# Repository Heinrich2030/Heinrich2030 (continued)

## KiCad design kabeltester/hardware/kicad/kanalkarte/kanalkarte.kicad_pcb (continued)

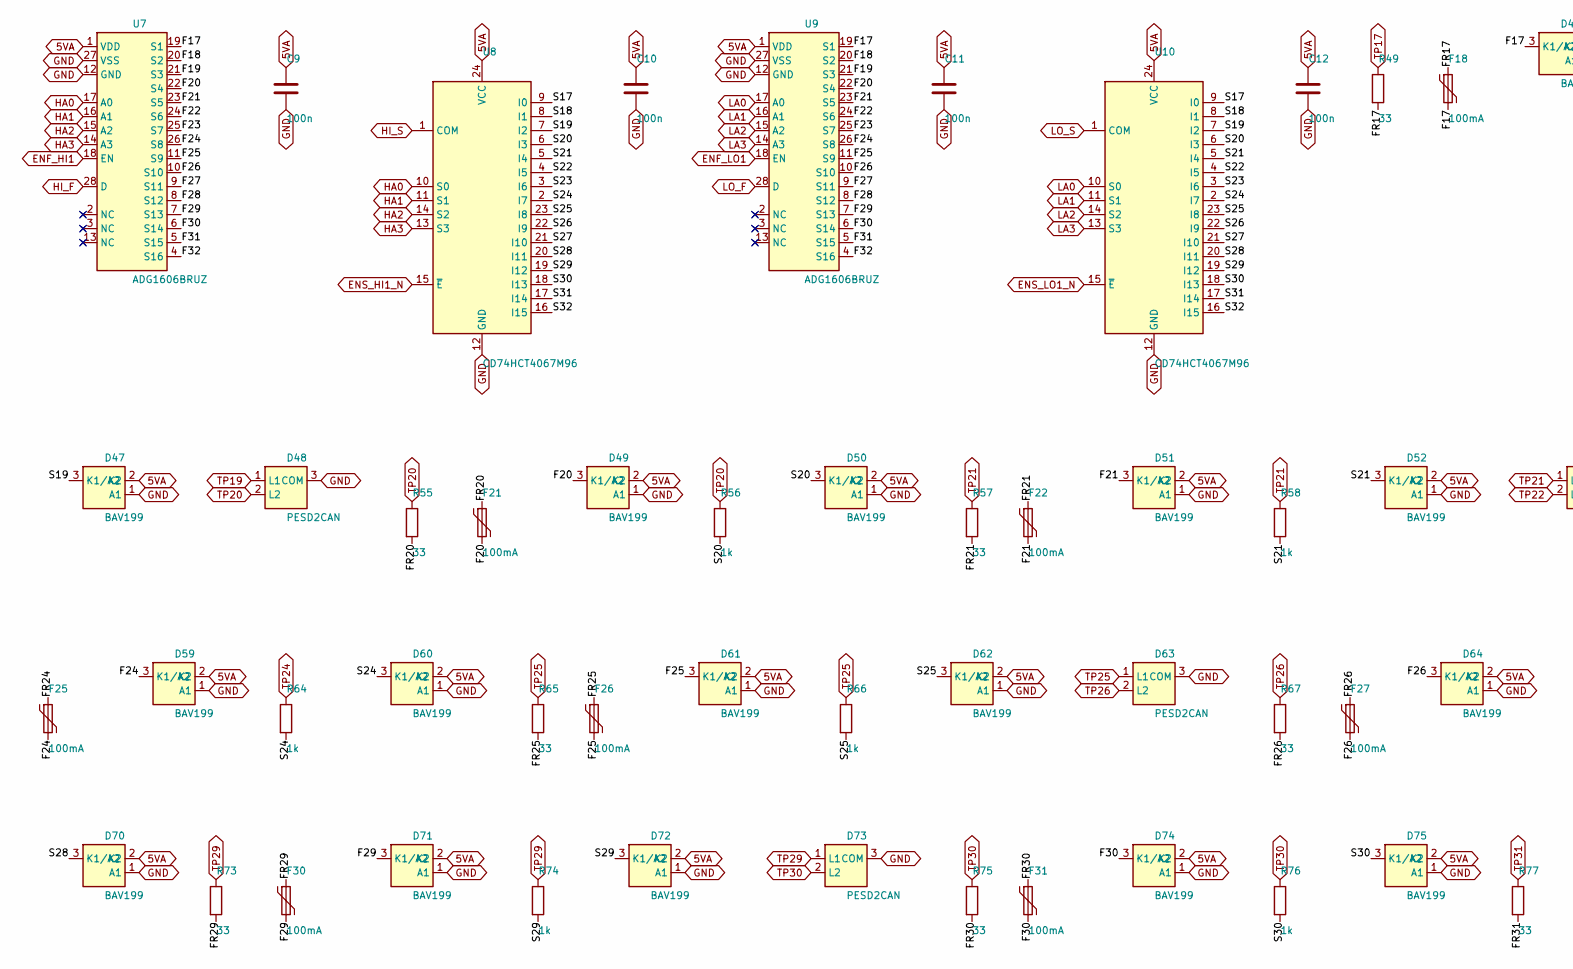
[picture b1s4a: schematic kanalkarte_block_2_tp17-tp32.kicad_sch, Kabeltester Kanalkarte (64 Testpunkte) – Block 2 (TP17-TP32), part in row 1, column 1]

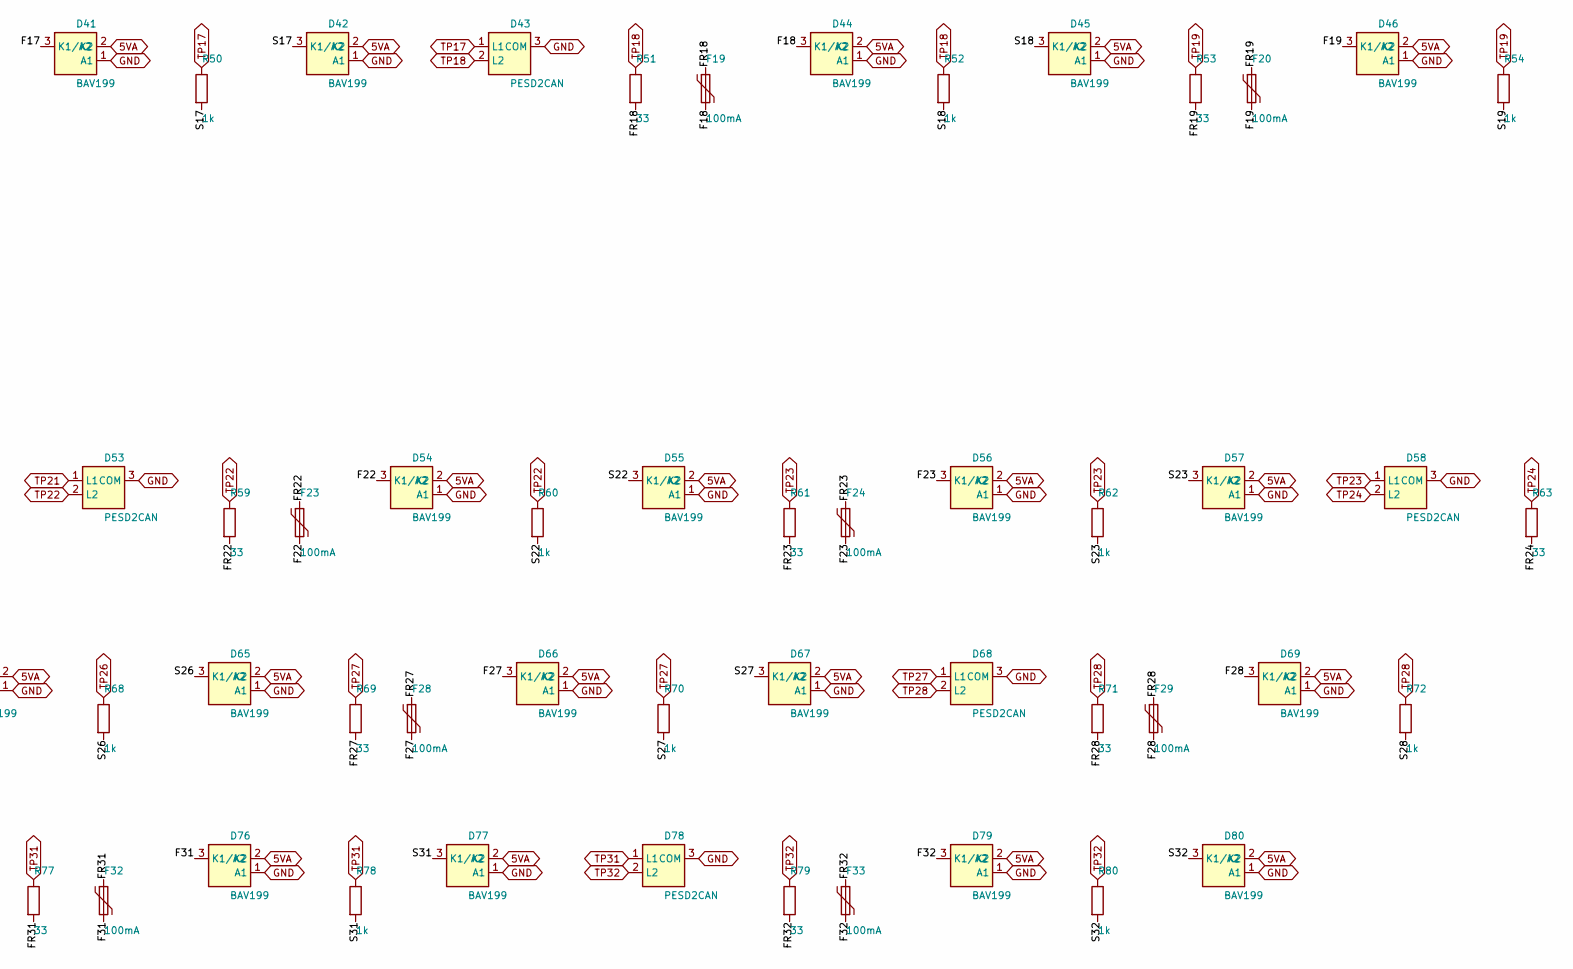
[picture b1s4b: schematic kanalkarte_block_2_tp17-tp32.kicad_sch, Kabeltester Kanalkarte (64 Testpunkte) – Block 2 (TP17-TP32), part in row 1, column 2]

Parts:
C9, C10, C11, C12: 100n; C_0603_1608Metric; LCSC C14663
D41, D42, D44, D45, D46, D47, D49, D50, D51, D52, D54, D55, D56, D57, D59, D60, D61, D62, D64, D65, D66, D67, D69, D70, D71, D72, D74, D75, D76, D77, D79, D80: BAV199; SOT-23
D43, D48, D53, D58, D63, D68, D73, D78: PESD2CAN; SOT-23
F18, F19, F20, F21, F22, F23, F24, F25, F26, F27, F28, F29, F30, F31, F32, F33: 100mA; Fuse_1206_3216Metric; MPN Bourns MF-USMF010-2
R49, R51, R53, R55, R57, R59, R61, R63, R65, R67, R69, R71, R73, R75, R77, R79: 33; R_1206_3216Metric; MPN CRCW120633R0FKEAHP
R50, R52, R54, R56, R58, R60, R62, R64, R66, R68, R70, R72, R74, R76, R78, R80: 1k; R_0603_1608Metric; LCSC C21190
U7, U9: ADG1606BRUZ; TSSOP-28_4.4x9.7mm_P0.65mm; LCSC C208204
U8, U10: CD74HCT4067M96; SOIC-24W_7.5x15.4mm_P1.27mm

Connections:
5VA: C9.1, C10.1, C11.1, C12.1, D41.2 (K2), D42.2 (K2), D44.2 (K2), D45.2 (K2), D46.2 (K2), D47.2 (K2), D49.2 (K2), D50.2 (K2), D51.2 (K2), D52.2 (K2), D54.2 (K2), D55.2 (K2), D56.2 (K2), D57.2 (K2), D59.2 (K2), D60.2 (K2), D61.2 (K2), D62.2 (K2), D64.2 (K2), D65.2 (K2), D66.2 (K2), D67.2 (K2), D69.2 (K2), D70.2 (K2), D71.2 (K2), D72.2 (K2), D74.2 (K2), D75.2 (K2), D76.2 (K2), D77.2 (K2), D79.2 (K2), D80.2 (K2), U7.1 (VDD), U8.24 (VCC), U9.1 (VDD), U10.24 (VCC); also elsewhere on the board
ENF_HI1: U7.18 (EN); also elsewhere on the board
ENF_LO1: U9.18 (EN); also elsewhere on the board
ENS_HI1_N: U8.15 (~E); also elsewhere on the board
ENS_LO1_N: U10.15 (~E); also elsewhere on the board
F17: D41.3 (K1/A2), F18.2, U7.19 (S1), U9.19 (S1)
F18: D44.3 (K1/A2), F19.2, U7.20 (S2), U9.20 (S2)
F19: D46.3 (K1/A2), F20.2, U7.21 (S3), U9.21 (S3)
F20: D49.3 (K1/A2), F21.2, U7.22 (S4), U9.22 (S4)
F21: D51.3 (K1/A2), F22.2, U7.23 (S5), U9.23 (S5)
F22: D54.3 (K1/A2), F23.2, U7.24 (S6), U9.24 (S6)
F23: D56.3 (K1/A2), F24.2, U7.25 (S7), U9.25 (S7)
F24: D59.3 (K1/A2), F25.2, U7.26 (S8), U9.26 (S8)
F25: D61.3 (K1/A2), F26.2, U7.11 (S9), U9.11 (S9)
F26: D64.3 (K1/A2), F27.2, U7.10 (S10), U9.10 (S10)
F27: D66.3 (K1/A2), F28.2, U7.9 (S11), U9.9 (S11)
F28: D69.3 (K1/A2), F29.2, U7.8 (S12), U9.8 (S12)
F29: D71.3 (K1/A2), F30.2, U7.7 (S13), U9.7 (S13)
F30: D74.3 (K1/A2), F31.2, U7.6 (S14), U9.6 (S14)
F31: D76.3 (K1/A2), F32.2, U7.5 (S15), U9.5 (S15)
F32: D79.3 (K1/A2), F33.2, U7.4 (S16), U9.4 (S16)
FR17: F18.1, R49.2
FR18: F19.1, R51.2
FR19: F20.1, R53.2
FR20: F21.1, R55.2
FR21: F22.1, R57.2
FR22: F23.1, R59.2
FR23: F24.1, R61.2
FR24: F25.1, R63.2
FR25: F26.1, R65.2
FR26: F27.1, R67.2
FR27: F28.1, R69.2
FR28: F29.1, R71.2
FR29: F30.1, R73.2
FR30: F31.1, R75.2
FR31: F32.1, R77.2
FR32: F33.1, R79.2
GND: C9.2, C10.2, C11.2, C12.2, D41.1 (A1), D42.1 (A1), D43.3 (COM), D44.1 (A1), D45.1 (A1), D46.1 (A1), D47.1 (A1), D48.3 (COM), D49.1 (A1), D50.1 (A1), D51.1 (A1), D52.1 (A1), D53.3 (COM), D54.1 (A1), D55.1 (A1), D56.1 (A1), D57.1 (A1), D58.3 (COM), D59.1 (A1), D60.1 (A1), D61.1 (A1), D62.1 (A1), D63.3 (COM), D64.1 (A1), D65.1 (A1), D66.1 (A1), D67.1 (A1), D68.3 (COM), D69.1 (A1), D70.1 (A1), D71.1 (A1), D72.1 (A1), D73.3 (COM), D74.1 (A1), D75.1 (A1), D76.1 (A1), D77.1 (A1), D78.3 (COM), D79.1 (A1), D80.1 (A1), U7.12 (GND), U7.27 (VSS), U8.12 (GND), U9.12 (GND), U9.27 (VSS), U10.12 (GND); also elsewhere on the board
HA0: U7.17 (A0), U8.10 (S0); also elsewhere on the board
HA1: U7.16 (A1), U8.11 (S1); also elsewhere on the board
HA2: U7.15 (A2), U8.14 (S2); also elsewhere on the board
HA3: U7.14 (A3), U8.13 (S3); also elsewhere on the board
HI_F: U7.28 (D); also elsewhere on the board
HI_S: U8.1 (COM); also elsewhere on the board
LA0: U9.17 (A0), U10.10 (S0); also elsewhere on the board
LA1: U9.16 (A1), U10.11 (S1); also elsewhere on the board
LA2: U9.15 (A2), U10.14 (S2); also elsewhere on the board
LA3: U9.14 (A3), U10.13 (S3); also elsewhere on the board
LO_F: U9.28 (D); also elsewhere on the board
LO_S: U10.1 (COM); also elsewhere on the board
S17: D42.3 (K1/A2), R50.2, U8.9 (I0), U10.9 (I0)
S18: D45.3 (K1/A2), R52.2, U8.8 (I1), U10.8 (I1)
S19: D47.3 (K1/A2), R54.2, U8.7 (I2), U10.7 (I2)
S20: D50.3 (K1/A2), R56.2, U8.6 (I3), U10.6 (I3)
S21: D52.3 (K1/A2), R58.2, U8.5 (I4), U10.5 (I4)
S22: D55.3 (K1/A2), R60.2, U8.4 (I5), U10.4 (I5)
S23: D57.3 (K1/A2), R62.2, U8.3 (I6), U10.3 (I6)
S24: D60.3 (K1/A2), R64.2, U8.2 (I7), U10.2 (I7)
S25: D62.3 (K1/A2), R66.2, U8.23 (I8), U10.23 (I8)
S26: D65.3 (K1/A2), R68.2, U8.22 (I9), U10.22 (I9)
S27: D67.3 (K1/A2), R70.2, U8.21 (I10), U10.21 (I10)
S28: D70.3 (K1/A2), R72.2, U8.20 (I11), U10.20 (I11)
S29: D72.3 (K1/A2), R74.2, U8.19 (I12), U10.19 (I12)
S30: D75.3 (K1/A2), R76.2, U8.18 (I13), U10.18 (I13)
S31: D77.3 (K1/A2), R78.2, U8.17 (I14), U10.17 (I14)
S32: D80.3 (K1/A2), R80.2, U8.16 (I15), U10.16 (I15)
TP17: D43.1 (L1), R49.1, R50.1; also elsewhere on the board
TP18: D43.2 (L2), R51.1, R52.1; also elsewhere on the board
TP19: D48.1 (L1), R53.1, R54.1; also elsewhere on the board
TP20: D48.2 (L2), R55.1, R56.1; also elsewhere on the board
TP21: D53.1 (L1), R57.1, R58.1; also elsewhere on the board
TP22: D53.2 (L2), R59.1, R60.1; also elsewhere on the board
TP23: D58.1 (L1), R61.1, R62.1; also elsewhere on the board
TP24: D58.2 (L2), R63.1, R64.1; also elsewhere on the board
TP25: D63.1 (L1), R65.1, R66.1; also elsewhere on the board
TP26: D63.2 (L2), R67.1, R68.1; also elsewhere on the board
TP27: D68.1 (L1), R69.1, R70.1; also elsewhere on the board
TP28: D68.2 (L2), R71.1, R72.1; also elsewhere on the board
TP29: D73.1 (L1), R73.1, R74.1; also elsewhere on the board
TP30: D73.2 (L2), R75.1, R76.1; also elsewhere on the board
TP31: D78.1 (L1), R77.1, R78.1; also elsewhere on the board
TP32: D78.2 (L2), R79.1, R80.1; also elsewhere on the board

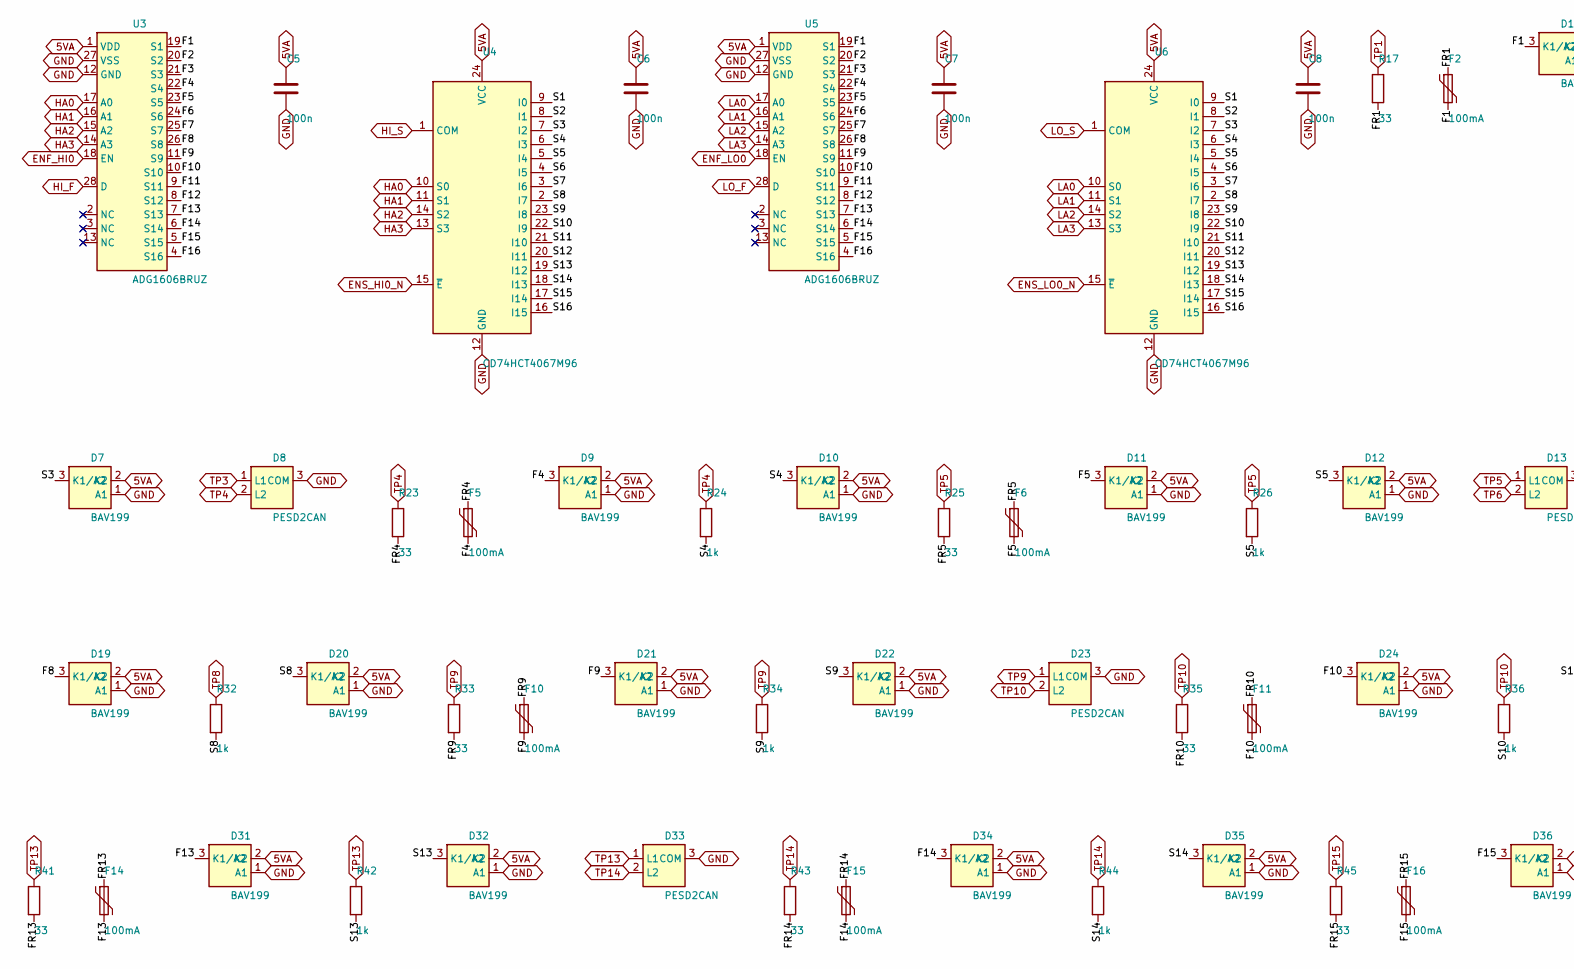
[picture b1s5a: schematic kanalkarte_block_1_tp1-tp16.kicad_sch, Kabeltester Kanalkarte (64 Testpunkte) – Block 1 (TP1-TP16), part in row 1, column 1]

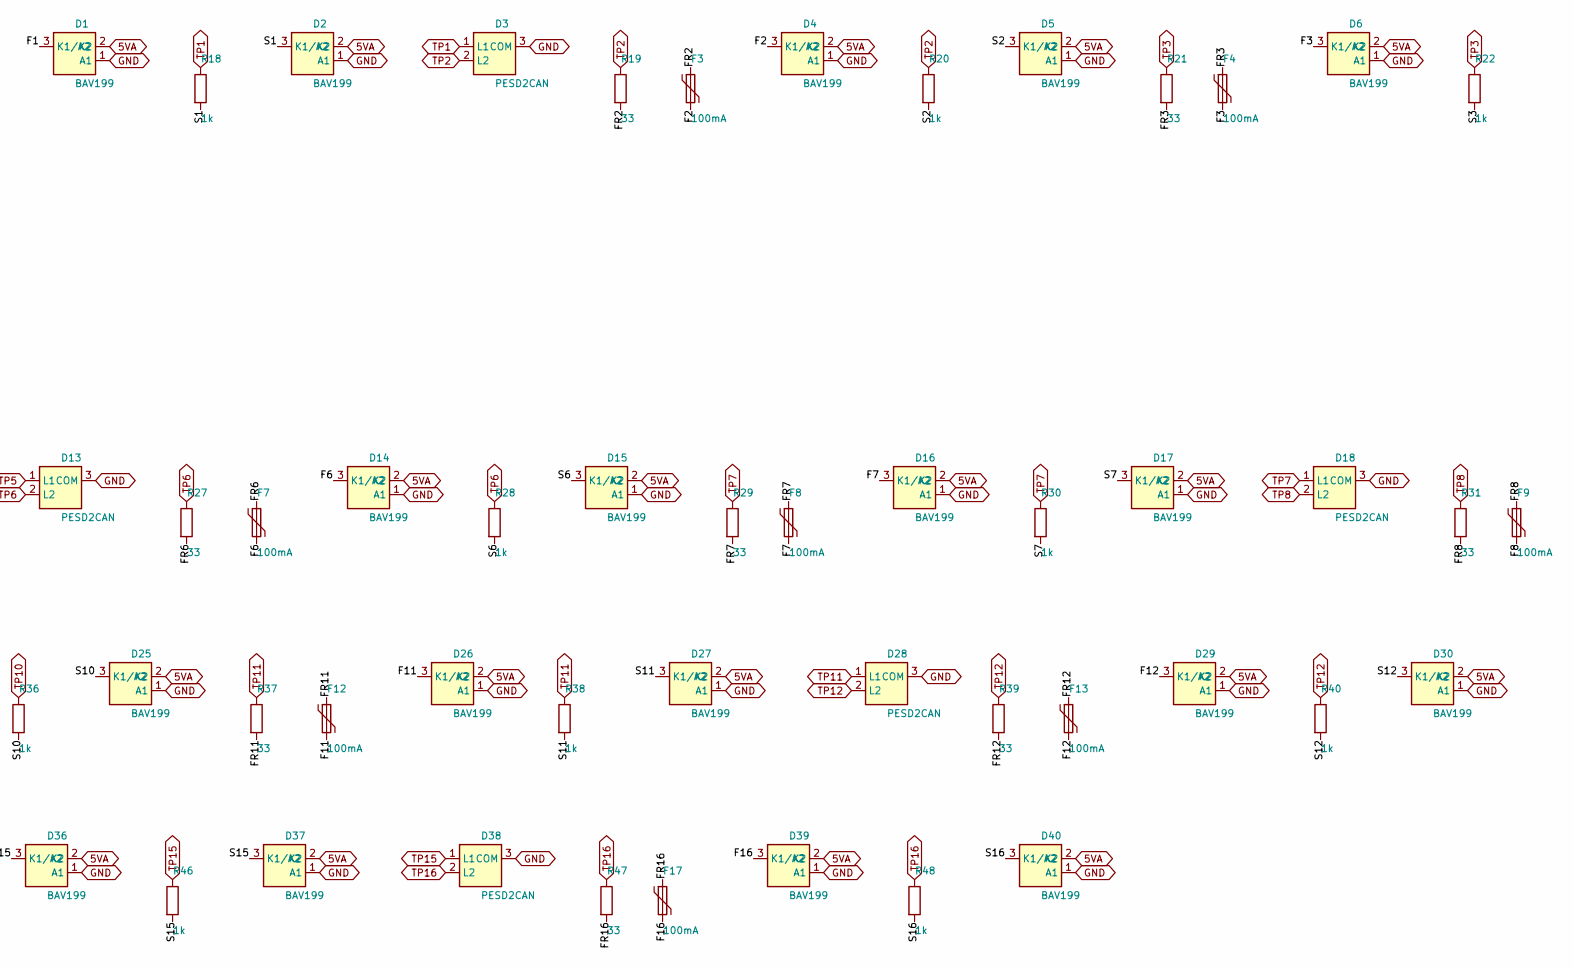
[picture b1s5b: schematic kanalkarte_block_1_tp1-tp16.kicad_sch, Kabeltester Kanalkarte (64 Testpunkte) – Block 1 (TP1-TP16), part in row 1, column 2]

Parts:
C5, C6, C7, C8: 100n; C_0603_1608Metric; LCSC C14663
D1, D2, D4, D5, D6, D7, D9, D10, D11, D12, D14, D15, D16, D17, D19, D20, D21, D22, D24, D25, D26, D27, D29, D30, D31, D32, D34, D35, D36, D37, D39, D40: BAV199; SOT-23
D3, D8, D13, D18, D23, D28, D33, D38: PESD2CAN; SOT-23
F2, F3, F4, F5, F6, F7, F8, F9, F10, F11, F12, F13, F14, F15, F16, F17: 100mA; Fuse_1206_3216Metric; MPN Bourns MF-USMF010-2
R17, R19, R21, R23, R25, R27, R29, R31, R33, R35, R37, R39, R41, R43, R45, R47: 33; R_1206_3216Metric; MPN CRCW120633R0FKEAHP
R18, R20, R22, R24, R26, R28, R30, R32, R34, R36, R38, R40, R42, R44, R46, R48: 1k; R_0603_1608Metric; LCSC C21190
U3, U5: ADG1606BRUZ; TSSOP-28_4.4x9.7mm_P0.65mm; LCSC C208204
U4, U6: CD74HCT4067M96; SOIC-24W_7.5x15.4mm_P1.27mm

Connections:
5VA: C5.1, C6.1, C7.1, C8.1, D1.2 (K2), D2.2 (K2), D4.2 (K2), D5.2 (K2), D6.2 (K2), D7.2 (K2), D9.2 (K2), D10.2 (K2), D11.2 (K2), D12.2 (K2), D14.2 (K2), D15.2 (K2), D16.2 (K2), D17.2 (K2), D19.2 (K2), D20.2 (K2), D21.2 (K2), D22.2 (K2), D24.2 (K2), D25.2 (K2), D26.2 (K2), D27.2 (K2), D29.2 (K2), D30.2 (K2), D31.2 (K2), D32.2 (K2), D34.2 (K2), D35.2 (K2), D36.2 (K2), D37.2 (K2), D39.2 (K2), D40.2 (K2), U3.1 (VDD), U4.24 (VCC), U5.1 (VDD), U6.24 (VCC); also elsewhere on the board
ENF_HI0: U3.18 (EN); also elsewhere on the board
ENF_LO0: U5.18 (EN); also elsewhere on the board
ENS_HI0_N: U4.15 (~E); also elsewhere on the board
ENS_LO0_N: U6.15 (~E); also elsewhere on the board
F1: D1.3 (K1/A2), F2.2, U3.19 (S1), U5.19 (S1)
F2: D4.3 (K1/A2), F3.2, U3.20 (S2), U5.20 (S2)
F3: D6.3 (K1/A2), F4.2, U3.21 (S3), U5.21 (S3)
F4: D9.3 (K1/A2), F5.2, U3.22 (S4), U5.22 (S4)
F5: D11.3 (K1/A2), F6.2, U3.23 (S5), U5.23 (S5)
F6: D14.3 (K1/A2), F7.2, U3.24 (S6), U5.24 (S6)
F7: D16.3 (K1/A2), F8.2, U3.25 (S7), U5.25 (S7)
F8: D19.3 (K1/A2), F9.2, U3.26 (S8), U5.26 (S8)
F9: D21.3 (K1/A2), F10.2, U3.11 (S9), U5.11 (S9)
F10: D24.3 (K1/A2), F11.2, U3.10 (S10), U5.10 (S10)
F11: D26.3 (K1/A2), F12.2, U3.9 (S11), U5.9 (S11)
F12: D29.3 (K1/A2), F13.2, U3.8 (S12), U5.8 (S12)
F13: D31.3 (K1/A2), F14.2, U3.7 (S13), U5.7 (S13)
F14: D34.3 (K1/A2), F15.2, U3.6 (S14), U5.6 (S14)
F15: D36.3 (K1/A2), F16.2, U3.5 (S15), U5.5 (S15)
F16: D39.3 (K1/A2), F17.2, U3.4 (S16), U5.4 (S16)
FR1: F2.1, R17.2
FR2: F3.1, R19.2
FR3: F4.1, R21.2
FR4: F5.1, R23.2
FR5: F6.1, R25.2
FR6: F7.1, R27.2
FR7: F8.1, R29.2
FR8: F9.1, R31.2
FR9: F10.1, R33.2
FR10: F11.1, R35.2
FR11: F12.1, R37.2
FR12: F13.1, R39.2
FR13: F14.1, R41.2
FR14: F15.1, R43.2
FR15: F16.1, R45.2
FR16: F17.1, R47.2
GND: C5.2, C6.2, C7.2, C8.2, D1.1 (A1), D2.1 (A1), D3.3 (COM), D4.1 (A1), D5.1 (A1), D6.1 (A1), D7.1 (A1), D8.3 (COM), D9.1 (A1), D10.1 (A1), D11.1 (A1), D12.1 (A1), D13.3 (COM), D14.1 (A1), D15.1 (A1), D16.1 (A1), D17.1 (A1), D18.3 (COM), D19.1 (A1), D20.1 (A1), D21.1 (A1), D22.1 (A1), D23.3 (COM), D24.1 (A1), D25.1 (A1), D26.1 (A1), D27.1 (A1), D28.3 (COM), D29.1 (A1), D30.1 (A1), D31.1 (A1), D32.1 (A1), D33.3 (COM), D34.1 (A1), D35.1 (A1), D36.1 (A1), D37.1 (A1), D38.3 (COM), D39.1 (A1), D40.1 (A1), U3.12 (GND), U3.27 (VSS), U4.12 (GND), U5.12 (GND), U5.27 (VSS), U6.12 (GND); also elsewhere on the board
HA0: U3.17 (A0), U4.10 (S0); also elsewhere on the board
HA1: U3.16 (A1), U4.11 (S1); also elsewhere on the board
HA2: U3.15 (A2), U4.14 (S2); also elsewhere on the board
HA3: U3.14 (A3), U4.13 (S3); also elsewhere on the board
HI_F: U3.28 (D); also elsewhere on the board
HI_S: U4.1 (COM); also elsewhere on the board
LA0: U5.17 (A0), U6.10 (S0); also elsewhere on the board
LA1: U5.16 (A1), U6.11 (S1); also elsewhere on the board
LA2: U5.15 (A2), U6.14 (S2); also elsewhere on the board
LA3: U5.14 (A3), U6.13 (S3); also elsewhere on the board
LO_F: U5.28 (D); also elsewhere on the board
LO_S: U6.1 (COM); also elsewhere on the board
S1: D2.3 (K1/A2), R18.2, U4.9 (I0), U6.9 (I0)
S2: D5.3 (K1/A2), R20.2, U4.8 (I1), U6.8 (I1)
S3: D7.3 (K1/A2), R22.2, U4.7 (I2), U6.7 (I2)
S4: D10.3 (K1/A2), R24.2, U4.6 (I3), U6.6 (I3)
S5: D12.3 (K1/A2), R26.2, U4.5 (I4), U6.5 (I4)
S6: D15.3 (K1/A2), R28.2, U4.4 (I5), U6.4 (I5)
S7: D17.3 (K1/A2), R30.2, U4.3 (I6), U6.3 (I6)
S8: D20.3 (K1/A2), R32.2, U4.2 (I7), U6.2 (I7)
S9: D22.3 (K1/A2), R34.2, U4.23 (I8), U6.23 (I8)
S10: D25.3 (K1/A2), R36.2, U4.22 (I9), U6.22 (I9)
S11: D27.3 (K1/A2), R38.2, U4.21 (I10), U6.21 (I10)
S12: D30.3 (K1/A2), R40.2, U4.20 (I11), U6.20 (I11)
S13: D32.3 (K1/A2), R42.2, U4.19 (I12), U6.19 (I12)
S14: D35.3 (K1/A2), R44.2, U4.18 (I13), U6.18 (I13)
S15: D37.3 (K1/A2), R46.2, U4.17 (I14), U6.17 (I14)
S16: D40.3 (K1/A2), R48.2, U4.16 (I15), U6.16 (I15)
TP1: D3.1 (L1), R17.1, R18.1; also elsewhere on the board
TP2: D3.2 (L2), R19.1, R20.1; also elsewhere on the board
TP3: D8.1 (L1), R21.1, R22.1; also elsewhere on the board
TP4: D8.2 (L2), R23.1, R24.1; also elsewhere on the board
TP5: D13.1 (L1), R25.1, R26.1; also elsewhere on the board
TP6: D13.2 (L2), R27.1, R28.1; also elsewhere on the board
TP7: D18.1 (L1), R29.1, R30.1; also elsewhere on the board
TP8: D18.2 (L2), R31.1, R32.1; also elsewhere on the board
TP9: D23.1 (L1), R33.1, R34.1; also elsewhere on the board
TP10: D23.2 (L2), R35.1, R36.1; also elsewhere on the board
TP11: D28.1 (L1), R37.1, R38.1; also elsewhere on the board
TP12: D28.2 (L2), R39.1, R40.1; also elsewhere on the board
TP13: D33.1 (L1), R41.1, R42.1; also elsewhere on the board
TP14: D33.2 (L2), R43.1, R44.1; also elsewhere on the board
TP15: D38.1 (L1), R45.1, R46.1; also elsewhere on the board
TP16: D38.2 (L2), R47.1, R48.1; also elsewhere on the board

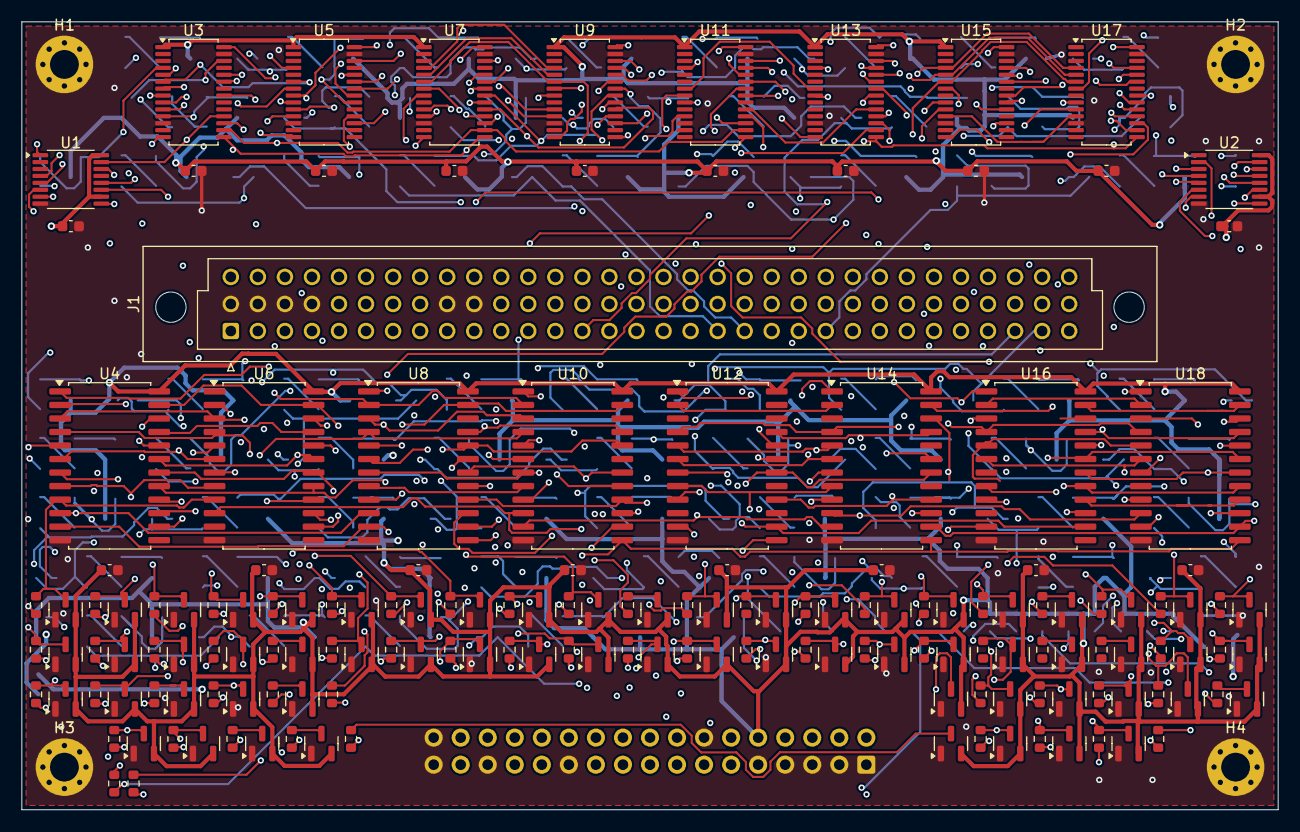
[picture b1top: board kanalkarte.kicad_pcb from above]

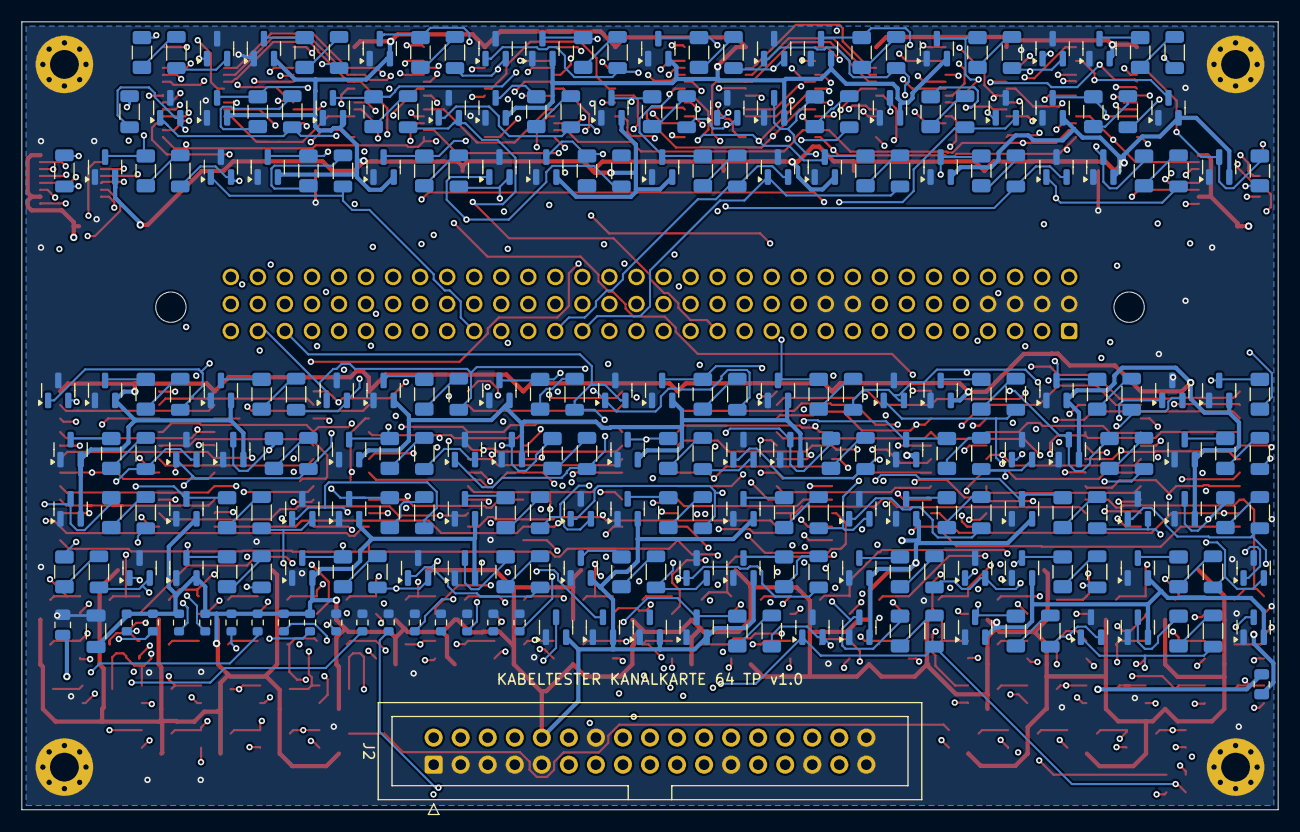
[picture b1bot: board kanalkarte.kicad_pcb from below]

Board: 6 copper layers, 118.0 x 74.0 mm, 413 parts (247 on the bottom side), 297 nets.

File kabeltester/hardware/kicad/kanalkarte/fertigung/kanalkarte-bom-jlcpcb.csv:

Comment,Designator,Footprint,Menge,Hersteller-Nr.,LCSC Part #
100n,"C1,C2,C5,C6,C7,C8,C9,C10,C11,C12,C13,C14,C15,C16,C17,C18,C19,C20",C_0603_1608Metric,18,,C14663
10u,C4,C_0805_2012Metric,1,,C15850
22u,C3,C_1206_3216Metric,1,,
DIN 41612 C96 Feder,J1,DIN41612_C_3x32_Female_Vertical_THT,1,Harting DIN-Signal C096 F gerade,
Messkarte,J2,IDC-Header_2x17_P2.54mm_Vertical,1,Wannenstecker 2x17,
50mA,F1,Fuse_0805_2012Metric,1,Bourns MF-PSMF005X-2,
100mA,"F2,F3,F4,F5,F6,F7,F8,F9,F10,F11,F12,F13,F14,F15,F16,F17,F18,F19,F20,F21,F22,F23,F24,F25,F26,F27,F28,F29,F30,F31,F32,F33,F34,F35,F36,F37,F38,F39,F40,F41,F42,F43,F44,F45,F46,F47,F48,F49,F50,F51,F52,F53,F54,F55,F56,F57,F58,F59,F60,F61,F62,F63,F64,F65",Fuse_1206_3216Metric,64,Bourns MF-USMF010-2,
CD74HCT4067M96,"U4,U6,U8,U10,U12,U14,U16,U18",SOIC-24W_7.5x15.4mm_P1.27mm,8,,
SN74HC595PW,"U1,U2",TSSOP-16_4.4x5mm_P0.65mm,2,,C5947
ADG1606BRUZ,"U3,U5,U7,U9,U11,U13,U15,U17",TSSOP-28_4.4x9.7mm_P0.65mm,8,,C208204
BAV199,"D1,D2,D4,D5,D6,D7,D9,D10,D11,D12,D14,D15,D16,D17,D19,D20,D21,D22,D24,D25,D26,D27,D29,D30,D31,D32,D34,D35,D36,D37,D39,D40,D41,D42,D44,D45,D46,D47,D49,D50,D51,D52,D54,D55,D56,D57,D59,D60,D61,D62,D64,D65,D66,D67,D69,D70,D71,D72,D74,D75,D76,D77,D79,D80,D81,D82,D84,D85,D86,D87,D89,D90,D91,D92,D94,D95,D96,D97,D99,D100,D101,D102,D104,D105,D106,D107,D109,D110,D111,D112,D114,D115,D116,D117,D119,D120,D121,D122,D124,D125,D126,D127,D129,D130,D131,D132,D134,D135,D136,D137,D139,D140,D141,D142,D144,D145,D146,D147,D149,D150,D151,D152,D154,D155,D156,D157,D159,D160",SOT-23,128,,
PESD2CAN,"D3,D8,D13,D18,D23,D28,D33,D38,D43,D48,D53,D58,D63,D68,D73,D78,D83,D88,D93,D98,D103,D108,D113,D118,D123,D128,D133,D138,D143,D148,D153,D158",SOT-23,32,,
10k,"R1,R2,R3,R4,R5,R6,R7,R8,R9,R10,R11,R12,R13,R14,R15,R16",R_0603_1608Metric,16,,C25804
1k,"R18,R20,R22,R24,R26,R28,R30,R32,R34,R36,R38,R40,R42,R44,R46,R48,R50,R52,R54,R56,R58,R60,R62,R64,R66,R68,R70,R72,R74,R76,R78,R80,R82,R84,R86,R88,R90,R92,R94,R96,R98,R100,R102,R104,R106,R108,R110,R112,R114,R116,R118,R120,R122,R124,R126,R128,R130,R132,R134,R136,R138,R140,R142,R144",R_0603_1608Metric,64,,C21190
33,"R17,R19,R21,R23,R25,R27,R29,R31,R33,R35,R37,R39,R41,R43,R45,R47,R49,R51,R53,R55,R57,R59,R61,R63,R65,R67,R69,R71,R73,R75,R77,R79,R81,R83,R85,R87,R89,R91,R93,R95,R97,R99,R101,R103,R105,R107,R109,R111,R113,R115,R117,R119,R121,R123,R125,R127,R129,R131,R133,R135,R137,R139,R141,R143",R_1206_3216Metric,64,CRCW120633R0FKEAHP,
